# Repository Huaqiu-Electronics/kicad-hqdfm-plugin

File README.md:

# HQ DFM

<p>
    English |<a href="README_CN.md">中文<a/>
</p>

### Implementing One-Click PCB Design Flaw Analysis with HQ DFM in KiCad

The HQ DFM plugin will assist you in:

- One-click analysis of over 20 design risk issues including open circuits, disconnected traces, line spacing, and width.
- Automatically analyzing PCB design flaws and eliminating production difficulties and design defects.

After checking the design flaws, you can use the NextPCB plugin to directly add them to your shopping cart at Huaqiu.

## Features

### Design Parameter Analysis

HQ DFM will analyze the following parameters in your KiCad design:

- Layer Count
- Dimensions
- Signal Integrity
- Smallest Trace Width
- Smallest Trace Spacing
- Pad size
- Pad Spacing
- Hatched Copper Pour
- Hole Diameter
- RingHole
- Drill Hole Spacing
- Drill to Copper
- Board Edge Clearance
- Special Drill Holes
- Holes on SMD Pads
- Missing SMask Openings
- Drill Hole Density
- Surface Finish Area
- Test Point Count

## Installation

Install the latest release plugin from **Plugin and Content Manager**. Open the "Plugin and Content Manager" from the main window, Navigate to the "Plugins" section and locate "HQ DFM" in the list. Finally, Click on the "Install" button and "Apply Pending Changes" to finalize the installation process.

### About HQ DFM

[HQ DFM](https://dfm.hqpcb.com/) is an efficient PCB design software that performs one-click analysis of design risks, provides optimization solutions, and generates Gerber, BOM, and coordinate files, making design and manufacturing simpler.

you can use the HQDFM Gerber Viewer to double check your manufacturing files, adjust board parameters then add it to your NextPCB cart directly.

### About HQ PCB / NextPCB

HQ PCB specializes in reliable multilayer PCB manufacture and assembly, and like KiCad, our goal is to enable engineers to build tomorrow's electronics. NextPCB is working with KiCad to provide smart tools to simplify the progression from design to physical product. With 3 major factories catering to prototyping, mass production and PCB assembly, and over 15 years of engineering expertise, NextPCB believes our industrial experience will prove invaluable to KiCad users and the PCB design community.

We are a [KiCad Platinum Sponsor](https://www.nextpcb.com/blog/kicad-nextpcb-platinum-sponsorship).

## kicad-HQ install

### Windows

The Windows installation package can be downloaded directly using the following link:
https://www.eda.cn/data/kicad-release/kicad-huaqiu-8.0.6-x86_64.exe.zip

### Linux
The Linux version requires Flatpak installation

#### 1，Install flatpak

`sudo apt install flatpak`

#### 2，Map a domain name to a specific IP address

`sudo vim /etc/hosts`

Use vim to go to etc/host and add this line：
`175.6.14.183 kicad.huaqiu.com`

Check whether the connection is successful:
`ping kicad.huaqiu.com`

#### 3，Add a remote kicad repository

`flatpak remote-add --user repo https://kicad.huaqiu.com/kicadhuaqiu`

Check whether the addition succeeds：
`flatpak remote-ls repo`

If GPG verification is reported, go to Step 4. Otherwise, skip it

#### 4，Ignore package unsigned authentication and modify the configuration with the vim editor

`vim ~/.local/share/flatpak/repo/config`

Modify in the file:
`gpg-verify=false`

`flatpak remote-modify --no-gpg-verify repo`

Check whether the addition is successful:
`flatpak remote-ls repo`

#### 5，Install kicad

`flatpak install repo org.kicad.KiCad`

If no dependency is reported, go to the next step "6".

#### 6，Lack of SDK dependency, use domestic flathub mirror warehouse, add remote warehouse first, and then install the missing dependency:

`sudo flatpak remote-modify flathub --url=https://mirror.sjtu.edu.cn/flathub`

In case of lack org.freedesktop.Sdk/x86_64/23.08：
`flatpak install flathub org.freedesktop.Sdk/x86_64/23.08`

In case of lack org.freedesktop.Sdk//23.08：
`flatpak install flathub org.freedesktop.Sdk//23.08`

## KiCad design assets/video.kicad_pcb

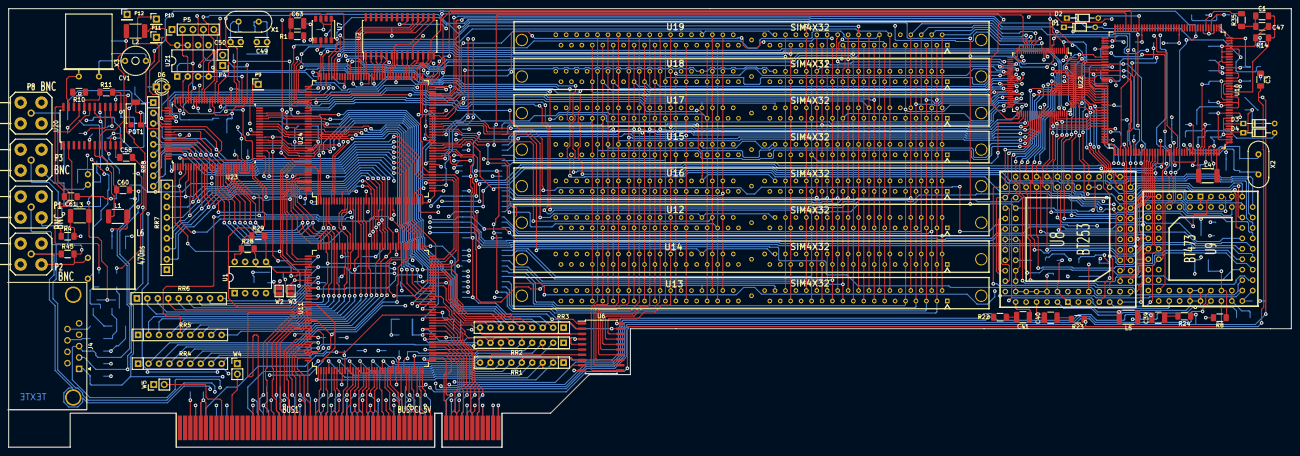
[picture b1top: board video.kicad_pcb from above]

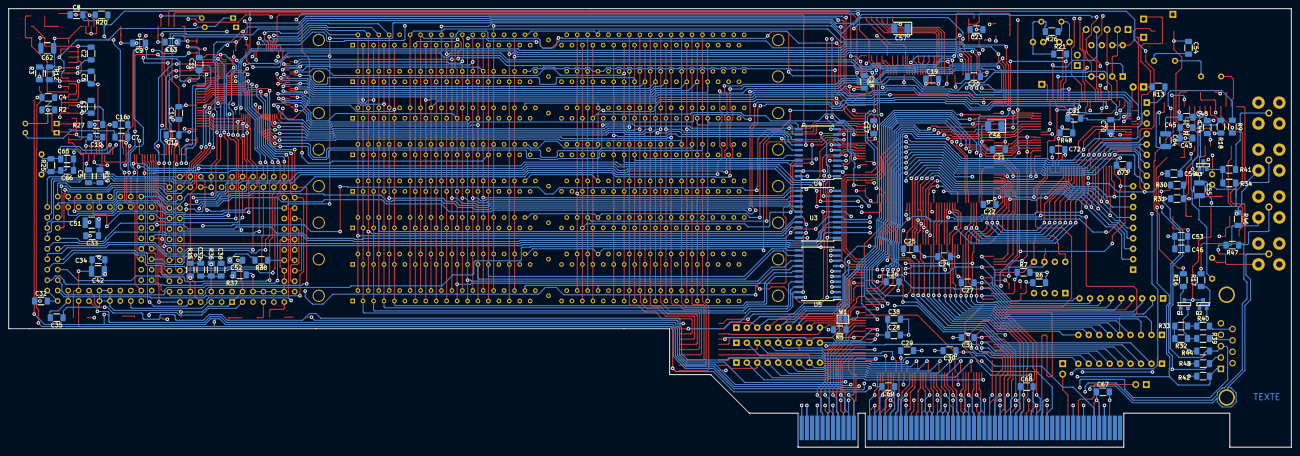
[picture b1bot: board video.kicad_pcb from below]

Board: 4 copper layers, 312.0 x 106.7 mm, 189 parts (103 on the bottom side), 371 nets.

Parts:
BUS1: BUSPCI_5V; BUSPCI
C1, C2, C3, C4, C5, C6, C7, C8, C9, C10, C11, C12, C13, C14, C15, C16, C17, C18, C19, C20, C21, C22, C23, C24, C25, C26, C27, C28, C29, C30, C31, C32, C33, C34, C35, C36, C70, C71, C72, C73: 100nF; R_1206_3216Metric_Pad1.30x1.75mm_HandSolder
C37: 100pF; R_1206_3216Metric_Pad1.30x1.75mm_HandSolder
C38, C67, C68, C69: 4,7uF; R_1206_3216Metric_Pad1.30x1.75mm_HandSolder
C39, C40, C41: 1uF; R_1210_3225Metric_Pad1.30x2.65mm_HandSolder
C42: 2.2uF; R_1210_3225Metric_Pad1.30x2.65mm_HandSolder
C43, C44, C45: 220nF; R_1206_3216Metric_Pad1.30x1.75mm_HandSolder
C46, C47: 220pF; R_1206_3216Metric_Pad1.30x1.75mm_HandSolder
C48: 22nF; R_1206_3216Metric_Pad1.30x1.75mm_HandSolder
C49, C50: 22pF; C_Disc_D3.0mm_W2.0mm_P2.50mm
C51: 22uF; R_1210_3225Metric_Pad1.30x2.65mm_HandSolder
C52: 22uF; R_1206_3216Metric_Pad1.30x1.75mm_HandSolder
C53: 330pF; R_1206_3216Metric_Pad1.30x1.75mm_HandSolder
C54: 4.7uF; R_1206_3216Metric_Pad1.30x1.75mm_HandSolder
C55: 4.7uF; R_1210_3225Metric_Pad1.30x2.65mm_HandSolder
C56, C57: 4.7uF; CP_EIA-3528-21_Kemet-B_Pad1.50x2.35mm_HandSolder
C58, C59, C60, C61: 47nF; R_1206_3216Metric_Pad1.30x1.75mm_HandSolder
C62, C63: 47uF; R_1210_3225Metric_Pad1.30x2.65mm_HandSolder
C64: 6,8uF; R_1210_3225Metric_Pad1.30x2.65mm_HandSolder
C65, C66: 22pF; R_1206_3216Metric_Pad1.30x1.75mm_HandSolder
CV1: 5/30pF; CV3-30PF
D1, D2, D3, D4: BAT46; D_DO-34_SOD68_P7.62mm_Horizontal
D6: LED; LED_D3.0mm
J4: DB9FEM; DSUB-9_Female_Horizontal_P2.77x2.84mm_EdgePinOffset14.56mm_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
L1: 2,2uH; R_1812_4532Metric_Pad1.30x3.40mm_HandSolder
L2, L3, L5: 22uH; R_1812_4532Metric_Pad1.30x3.40mm_HandSolder
L4: 22uF; R_1812_4532Metric_Pad1.30x3.40mm_HandSolder
L6: 470ns; LRTDK
P1, P2, P3, P8: BNC; subclick
P4: CONN_2; PinHeader_1x02_P2.54mm_Vertical
P5: CONN_5; PinHeader_1x05_P2.54mm_Vertical
P9, P10, P11, P12: CONN_1; PinHeader_1x01_P2.54mm_Vertical
POT1: 100K; Potentiometer_Bourns_3314G_Vertical
Q1, Q2, Q3: BC848; SOT23EBC
R1: 10; R_1206_3216Metric_Pad1.30x1.75mm_HandSolder
R2, R3: 100; R_1206_3216Metric_Pad1.30x1.75mm_HandSolder
R4, R5, R6, R7, R48: 10K; R_1206_3216Metric_Pad1.30x1.75mm_HandSolder
R8: 150; R_1206_3216Metric_Pad1.30x1.75mm_HandSolder
R9: 150K; R_1206_3216Metric_Pad1.30x1.75mm_HandSolder
R10, R11, R12, R13: 1K; R_1206_3216Metric_Pad1.30x1.75mm_HandSolder
R14, R15: 1M; R_1206_3216Metric_Pad1.30x1.75mm_HandSolder
R16, R17, R18, R19, R20, R21, R22, R23, R24: 220; R_1206_3216Metric_Pad1.30x1.75mm_HandSolder
R25, R26: 220K; R_1206_3216Metric_Pad1.30x1.75mm_HandSolder
R27: 27K; R_1206_3216Metric_Pad1.30x1.75mm_HandSolder
R28, R29: 2,2K; R_1206_3216Metric_Pad1.30x1.75mm_HandSolder
R30: 3,3K; R_1206_3216Metric_Pad1.30x1.75mm_HandSolder
R31, R32, R33, R34, R35, R36: 470; R_1206_3216Metric_Pad1.30x1.75mm_HandSolder
R37, R38: 510; R_1206_3216Metric_Pad1.30x1.75mm_HandSolder
R39, R40, R41: 68; R_1206_3216Metric_Pad1.30x1.75mm_HandSolder
R42, R43, R44, R45, R46, R47: 75; R_1206_3216Metric_Pad1.30x1.75mm_HandSolder
RR1, RR2, RR3, RR4, RR5, RR6, RR7, RR8: 8x10K; R_Array_SIP9
U1: 24C16; DIP-8_W7.62mm
U2: 4C4001; SOIC-28W_7.5x17.9mm_P1.27mm
U3, U4, U5, U6: 74LS245; SOIC-20W_7.5x12.8mm_P1.27mm
U7: AV9173; SSOP-8_3.95x5.21x3.27mm_P1.27mm
U8: BT253; PLCC84
U9: BT473; PLCC68
U10: BT812; PQFP-160_28x28mm_P0.65mm
U11: S5933_PQ160; PQFP-160_28x28mm_P0.65mm
U12, U13, U14, U15, U16, U17, U18, U19: SIM4X32; sim72
U20: TDA8501; SOIC-24W_7.5x15.4mm_P1.27mm
U21: XC1736APD8; DIP-8_W7.62mm
U22: XC4003-VQ100; TQFP-100_14x14mm_P0.5mm
U23: XC4003/PQ100; PQFP-100_14x20mm_P0.65mm
U24: XC4005-PQ160; PQFP-160_28x28mm_P0.65mm
W1: 16/32; SolderJumper-2_P1.3mm_Open_Pad1.0x1.5mm
W2: FLOAT#; SolderJumper-2_P1.3mm_Open_Pad1.0x1.5mm
W3: SERNV; SolderJumper-2_P1.3mm_Open_Pad1.0x1.5mm
W4, W5: TEST; PinHeader_1x02_P2.54mm_Vertical
X1: 10MHz; Crystal_HC18-U_Vertical
X2: 30MHz; Crystal_HC18-U_Vertical
X3: 4.433618MHz; Crystal_HC18-U_Horizontal

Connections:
+3.3V: BUS1.A21 (+3.3V), BUS1.A27 (+3.3V), BUS1.A33 (+3.3V), BUS1.A39 (+3.3V), BUS1.A45 (+3.3V), BUS1.A53 (+3.3V), BUS1.B25 (+3.3V), BUS1.B31 (+3.3V), BUS1.B36 (+3.3V), BUS1.B41 (+3.3V), BUS1.B43 (+3.3V), BUS1.B54 (+3.3V), C68.1, C69.1
+5F: C55.1, L3.2, Q1.3 (C), Q2.3 (C), Q3.3 (C)
+5V: BUS1.A5 (+5V), BUS1.A8 (+5V), BUS1.A10 (VIO), BUS1.A16 (VIO), BUS1.A59 (VIO), BUS1.A61 (+5V), BUS1.A62 (+5V), BUS1.B5 (+5V), BUS1.B6 (+5V), BUS1.B19 (VIO), BUS1.B59 (VIO), BUS1.B61 (+5V), BUS1.B62 (+5V), C9.1, C10.1, C11.1, C15.1, C17.1, C18.1, C19.1, C20.1, C21.1, C22.1, C24.1, C25.1, C26.1, C27.1, C28.1, C29.1, C30.1, C31.1, C38.1, C56.1, C57.1, C67.1, C70.1, C71.1, C72.1, C73.1, D2.2 (K), D4.2 (K), L2.1, L3.1, L4.1, L5.1, R1.2, R4.2, R5.2, R6.2, R7.2, R13.1, R28.1, R29.1, R48.1, RR1.1 (COM), RR2.1 (COM), RR3.1 (COM), RR4.1 (COM), RR5.1 (COM), RR6.1 (COM), RR7.1 (COM), RR8.1 (COM), U1.7 (WP), U1.8 (VCC), U2.10 (VCC), U3.20 (VCC), U4.20 (VCC), U5.20 (VCC), U6.20 (VCC), U10.31 (VCC), U10.45 (VCC), U10.57 (VCC), U10.76 (VCC), U10.91 (VCC), U10.102 (VCC), U10.112 (VCC), U11.11 (VCC), U11.31 (VCC), U11.51 (VCC), U11.71 (VCC), U11.91 (VCC), U11.111 (VCC), U11.131 (VCC), U11.151 (VCC), U12.10 (VCC), U12.30 (VCC), U12.59 (VCC), U13.10 (VCC), U13.30 (VCC), U13.59 (VCC), U14.10 (VCC), U14.30 (VCC), U14.59 (VCC), U15.10 (VCC), U15.30 (VCC), U15.59 (VCC), U16.10 (VCC), U16.30 (VCC), U16.59 (VCC), U17.10 (VCC), U17.30 (VCC), U17.59 (VCC), U18.10 (VCC), U18.30 (VCC), U18.59 (VCC), U19.10 (VCC), U19.30 (VCC), U19.59 (VCC), U21.7 (VPP), U21.8 (VCC), U22.12 (VCC), U22.22 (M1/RD), U22.24 (M0/RT), U22.25 (VCC), U22.26 (M2), U22.37 (VCC), U22.51 (VCC), U22.63 (VCC), U22.75 (VCC), U22.89 (VCC), U22.100 (VCC), U23.3 (VCC), U23.15 (VCC), U23.28 (VCC), U23.40 (VCC), U23.54 (VCC), U23.66 (VCC), U23.78 (VCC), U23.92 (VCC), U24.20 (VCC), U24.38 (M1), U24.40 (M0), U24.41 (VCC), U24.42 (M2), U24.60 (VCC), U24.81 (VCC), U24.100 (VCC), U24.120 (VCC), U24.142 (VCC), U24.160 (VCC)
/ACCES_RAM-: U3.19 (CE), U4.19 (CE), U5.19 (CE), U6.19 (CE), U22.21 (SGCK2), U24.56
/ACQ_ON: U22.13, U24.48 (LDC)
/ADR2: U11.68 (ADR2), U23.48, U24.137
/ADR3: U11.67 (ADR3), U23.44, U24.138
/ADR4: U11.66 (ADR4), U23.43, U24.139
/ADR5: U11.64 (ADR5), U23.42, U24.140
/ADR6: U11.132 (ADR6), U23.39 (P39/INIT), U24.143
/BE-0: U11.87 (BE0#), U23.38, U24.144
/BE-1: U11.63 (BE1#), U23.37, U24.145
/BE-2: U11.62 (BE2#), U23.36, U24.146
/BE-3: U11.60 (BE3#), U23.35, U24.147
/BLANK-: U9.7 (BLANK), U22.8, U24.53
/BLUE_IN: P3.1 (In), R22.1, R46.1
/BLUE_OUT: C60.2, J4.3, R44.2, U9.39 (BLU)
/BPCLK: U11.140 (BPCLK), U23.30 (PGCK2)
/BT812_RD-: U10.86 (RD), U23.71
/BT812_WR-: U10.83 (WR), U23.70
/CAS0-: U12.40 (CAS0), U13.40 (CAS0), U14.40 (CAS0), U15.40 (CAS0), U16.40 (CAS0), U17.40 (CAS0), U18.40 (CAS0), U19.40 (CAS0), U24.57
/CAS1-: U12.41 (CAS1), U13.41 (CAS1), U14.41 (CAS1), U15.41 (CAS1), U16.41 (CAS1), U17.41 (CAS1), U18.41 (CAS1), U19.41 (CAS1), U24.58
/CAS2-: U12.42 (CAS2), U13.42 (CAS2), U14.42 (CAS2), U15.42 (CAS2), U16.42 (CAS2), U17.42 (CAS2), U18.42 (CAS2), U19.42 (CAS2), U24.59 (P59-INIT)
/CAS3-: U12.43 (CAS3), U13.43 (CAS3), U14.43 (CAS3), U15.43 (CAS3), U16.43 (CAS3), U17.43 (CAS3), U18.43 (CAS3), U19.43 (CAS3), U24.62
/CLAMP: U8.37 (ZERO), U8.59 (CLAMP), U22.7, U24.75
/CLKCAD: U8.38 (BCLOCK), U8.39 (GCLOCK), U8.40 (RCLOCK), U22.2 (PGCK1), U24.77
/CLKCDA: U9.9 (CLOCK), U22.79 (PGCK4), U24.76
/CSYNC-OUT: R30.2, U9.8 (SYNC), U22.9 (P/A15), U24.13 (TMS)
/CSYNCIN-: U8.8 (CSYNC), U24.54
/C_OUT: J4.8, R39.1
/DQ0: RR7.2, U3.2 (A0), U8.16 (D0), U9.14 (D0), U10.92 (D0), U11.100 (DQ0), U23.13, U24.21
/DQ1: RR7.3, U3.3 (A1), U8.15 (D1), U9.15 (D1), U10.93 (D1), U11.99 (DQ1), U23.12, U24.22
/DQ2: RR7.4, U3.4 (A2), U8.14 (D2), U9.16 (D2), U10.94 (D2), U11.98 (DQ2), U23.11, U24.23
/DQ3: RR7.5, U3.5 (A3), U8.13 (D3), U9.17 (D3), U10.95 (D3), U11.96 (DQ3), U23.7 (P7/TDI), U24.24
/DQ4: RR7.6, U3.6 (A4), U8.12 (D4), U9.18 (D4), U10.96 (D4), U11.95 (DQ4), U23.9 (P9/TMS), U24.25
/DQ5: RR7.7, U3.7 (A5), U8.11 (D5), U9.19 (D5), U10.97 (D5), U11.94 (DQ5), U23.8 (P8/TCK), U24.26
/DQ6: RR7.8, U3.8 (A6), U8.10 (D6), U9.20 (D6), U10.99 (D6), U11.92 (DQ6), U23.6, U24.27
/DQ7: RR7.9, U3.9 (A7), U8.9 (D7), U9.21 (D7), U10.100 (D7), U11.88 (DQ7), U23.5 (PGCK1), U24.28
/DQ8: RR8.9, U4.2 (A0), U11.86 (DQ8), U23.97, U24.32
/DQ9: RR8.8, U4.3 (A1), U11.84 (DQ9), U23.96, U24.33
/DQ10: RR8.7, U4.4 (A2), U11.83 (DQ10), U23.95, U24.34
/DQ11: RR8.6, U4.5 (A3), U11.82 (DQ11), U23.94, U24.35
/DQ12: RR8.5, U4.6 (A4), U11.80 (DQ12), U23.93, U24.36
/DQ13: RR8.4, U4.7 (A5), U11.79 (DQ13), U23.90, U24.45
/DQ14: RR8.3, U4.8 (A6), U11.78 (DQ14), U23.88, U24.46
/DQ15: RR8.2, U4.9 (A7), U11.76 (DQ15), U23.89, U24.47
/DQ16: RR4.7, U5.2 (A0), U11.157 (DQ16)
/DQ17: RR4.9, U5.3 (A1), U11.145 (DQ17)
/DQ18: RR6.6, U5.4 (A2), U11.133 (DQ18)
/DQ19: RR6.8, U5.5 (A3), U11.125 (DQ19)
/DQ20: RR6.3, U5.6 (A4), U11.117 (DQ20)
/DQ21: RR5.6, U5.7 (A5), U11.105 (DQ21)
/DQ22: RR4.3, U5.8 (A6), U11.93 (DQ22)
/DQ23: RR4.5, U5.9 (A7), U11.85 (DQ23)
/DQ24: RR3.3, U6.2 (A0), U11.77 (DQ24)
/DQ25: RR3.9, U6.3 (A1), U11.65 (DQ25)
/DQ26: RR2.8, U6.4 (A2), U11.53 (DQ26)
/DQ27: RR2.5, U6.5 (A3), U11.45 (DQ27)
/DQ28: RR2.3, U6.6 (A4), U11.37 (DQ28)
/DQ29: RR1.8, U6.7 (A5), U11.25 (DQ29)
/DQ30: RR1.5, U6.8 (A6), U11.13 (DQ30)
/DQ31: RR1.3, U6.9 (A7), U11.5 (DQ31)
/ESVIDEO-RVB/OE_RVB-: U8.57 (OE), U9.29 (CR2)
/ESVIDEO-RVB/REF+: R37.2, U8.64 (BREF+), U8.65 (GREF+), U8.66 (RREF+), U8.71 (IOUT5), U8.73 (IOUT4), U8.76 (IOUT3), U8.78 (IOUT2), U8.80 (IOUT1), U8.82 (IOUT0)
/ESVIDEO-RVB/VAA: C33.1, C34.1, C35.1, C42.1, C51.1, C52.1, L5.2, U8.1 (VAA), U8.43 (VAA), U8.44 (VAA), U8.84 (VAA), U9.1 (VAA), U9.2 (VAA), U9.33 (VAA), U9.34 (VAA), U9.35 (VAA), U9.36 (VAA)
/F_PALIN: U10.104 (CLKX1), U24.43 (PGCK2)
/GREEN_IN: C3.2, P2.1 (In), R23.1, R45.1
/GREEN_OUT: C59.2, J4.2, R43.2, U9.38 (GRE)
/HD_PAL-: U10.36 (HRESET), U24.52
/IRQ-: U11.124 (IRQ#), U24.149
/IRQ_SRL: RR2.7, U11.57 (EA0), U24.134
/MXA0: U12.12 (A0), U13.12 (A0), U14.12 (A0), U15.12 (A0), U16.12 (A0), U17.12 (A0), U18.12 (A0), U19.12 (A0), U24.128
/MXA1: U12.13 (A1), U13.13 (A1), U14.13 (A1), U15.13 (A1), U16.13 (A1), U17.13 (A1), U18.13 (A1), U19.13 (A1), U24.127
/MXA2: U12.14 (A2), U13.14 (A2), U14.14 (A2), U15.14 (A2), U16.14 (A2), U17.14 (A2), U18.14 (A2), U19.14 (A2), U24.126
/MXA3: U12.15 (A3), U13.15 (A3), U14.15 (A3), U15.15 (A3), U16.15 (A3), U17.15 (A3), U18.15 (A3), U19.15 (A3), U24.125
/MXA4: U12.16 (A4), U13.16 (A4), U14.16 (A4), U15.16 (A4), U16.16 (A4), U17.16 (A4), U18.16 (A4), U19.16 (A4), U24.124
/MXA5: U12.17 (A5), U13.17 (A5), U14.17 (A5), U15.17 (A5), U16.17 (A5), U17.17 (A5), U18.17 (A5), U19.17 (A5), U24.123
/MXA6: U12.18 (A6), U13.18 (A6), U14.18 (A6), U15.18 (A6), U16.18 (A6), U17.18 (A6), U18.18 (A6), U19.18 (A6), U24.116
/MXA7: U12.28 (A7), U13.28 (A7), U14.28 (A7), U15.28 (A7), U16.28 (A7), U17.28 (A7), U18.28 (A7), U19.28 (A7), U24.115
/MXA8: U12.31 (A8), U13.31 (A8), U14.31 (A8), U15.31 (A8), U16.31 (A8), U17.31 (A8), U18.31 (A8), U19.31 (A8), U24.114 (P114-RDY)
/MXA9: U12.32 (A9), U13.32 (A9), U14.32 (A9), U15.32 (A9), U16.32 (A9), U17.32 (A9), U18.32 (A9), U19.32 (A9), U24.113
/MXA10: U12.19 (A10), U13.19 (A10), U14.19 (A10), U15.19 (A10), U16.19 (A10), U17.19 (A10), U18.19 (A10), U19.19 (A10), U24.109
/OE_PAL-: U9.28 (CR1), U10.46 (VTU_EN), U10.47 (PIXEL_EN)
/PCA0: U8.17 (A0), U9.24 (RS0), U10.84 (RS0), U23.65
/PCA1: U8.18 (A1), U9.25 (RS1), U10.85 (RS1), U23.64
/PCA2: U8.19 (A2), U9.26 (RS2), U23.63
/PTADR-: RR5.5, U11.107 (PTADR#), U23.24 (SGCK2), U24.14
/PTATN-: RR5.2, U11.114 (PTATN#), U23.18, U24.4
/PTBE-0: U11.116 (PTBE0#), U23.20, U24.158
/PTBE-1: U11.118 (PTBE1#), U23.21, U24.157
/PTBE-2: U11.119 (PTBE2#), U23.22, U24.156
/PTBE-3: U11.120 (PTBE3#), U23.23, U24.155
/PTBURST: U11.112 (PTBURST#), U23.17, U24.5
/PTNUM0: U11.123 (PTNUM0), U23.34, U24.150
/PTNUM1: U11.122 (PTNUM1), U23.32, U24.154
/PTRDY-: RR6.2, U11.115 (PTRDY#), U23.19, U24.3
/PTWR: U11.108 (PTWR), U23.16, U24.12
/RAS0-: U19.34 (RAS2), U19.44 (RAS0), U24.74
/RAS1-: U18.34 (RAS2), U18.44 (RAS0), U24.73
/RAS2-: U17.34 (RAS2), U17.44 (RAS0), U24.69
/RAS3-: U15.34 (RAS2), U15.44 (RAS0), U24.68
/RAS4-: U16.34 (RAS2), U16.44 (RAS0), U24.67
/RAS5-: U12.34 (RAS2), U12.44 (RAS0), U24.66
/RAS6-: U14.34 (RAS2), U14.44 (RAS0), U24.65
/RAS7-: U13.34 (RAS2), U13.44 (RAS0), U24.64
/RDCAD-: U8.20 (RD), U23.74 (P74/BUSY)
/RDCDA-: U9.22 (WR), U23.72
/RDEMPTY: U11.106 (RDEMPTY), U24.15
/RDFIFO-: RR5.7, U11.104 (RDFIFO#), U24.16
/RED_IN: C4.2, P1.1 (In), R24.1, R47.1
/RED_OUT: C58.2, J4.1, R42.2, U9.37 (RED)
/SELECT-: RR3.4, U11.75 (SELECT#), U23.45, U24.135
/SYSRST-: U10.87 (RESET), U11.126 (SYSRST#), U23.1, U24.148
/TVB0: U8.32 (B0), U9.61 (B0), U10.55 (B0), U22.92
/TVB1: U8.31 (B1), U9.62 (B1), U10.54 (B1), U22.93
/TVB2: U8.30 (B2), U9.63 (B2), U10.53 (B2), U22.94
/TVB3: U8.29 (B3), U9.64 (B3), U10.52 (B3), U22.95 (P91)
/TVB4: U8.28 (B4), U9.65 (B4), U10.51 (B4), U22.96
/TVB5: U8.27 (B5), U9.66 (B5), U10.50 (B5), U22.97
/TVB6: U8.26 (B6), U9.67 (B6), U10.49 (B6), U22.98
/TVB7: U8.25 (B7), U9.68 (B7), U10.48 (B7), U22.99 (SGCK1)
/TVG0: U8.48 (G0), U9.53 (G0), U10.74 (G0), U22.67
/TVG1: U8.47 (G1), U9.54 (G1), U10.73 (G1), U22.68
/TVG2: U8.46 (G2), U9.55 (G2), U10.72 (G2), U22.69
/TVG3: U8.45 (G3), U9.56 (G3), U10.71 (G3), U22.70
/TVG4: U8.36 (G4), U9.57 (G4), U10.70 (G4), U22.71 (P71/RDY)
/TVG5: U8.35 (G5), U9.58 (G5), U10.69 (G5), U22.78
/TVG6: U8.34 (G6), U9.59 (G6), U10.68 (G6), U22.80
/TVG7: U8.33 (G7), U9.60 (G7), U10.67 (G7), U22.81
/TVI0: U9.10 (OL0), U24.108
/TVI1: U9.11 (OL1), U24.107
/TVR0: U8.56 (R0), U9.45 (R0), U10.65 (R0), U22.82
/TVR1: U8.55 (R1), U9.46 (R1), U10.64 (R1), U22.83
/TVR2: U8.54 (R2), U9.47 (R2), U10.63 (R2), U22.84
/TVR3: U8.53 (R3), U9.48 (R3), U10.62 (R3), U22.85
/TVR4: U8.52 (R4), U9.49 (R4), U10.61 (R4), U22.86
/TVR5: U8.51 (R5), U9.50 (R5), U10.60 (R5), U22.87
/TVR6: U8.50 (R6), U9.51 (R6), U10.59 (R6), U22.90
/TVR7: U8.49 (R7), U9.52 (R7), U10.58 (R7), U22.91
/TVRAM0: U3.18 (B0), U12.2 (DQ0), U13.2 (DQ0), U14.2 (DQ0), U15.2 (DQ0), U16.2 (DQ0), U17.2 (DQ0), U18.2 (DQ0), U19.2 (DQ0), U22.17
/TVRAM1: U3.17 (B1), U12.4 (DQ1), U13.4 (DQ1), U14.4 (DQ1), U15.4 (DQ1), U16.4 (DQ1), U17.4 (DQ1), U18.4 (DQ1), U19.4 (DQ1), U22.19
/TVRAM2: U3.16 (B2), U12.6 (DQ2), U13.6 (DQ2), U14.6 (DQ2), U15.6 (DQ2), U16.6 (DQ2), U17.6 (DQ2), U18.6 (DQ2), U19.6 (DQ2), U22.20
/TVRAM3: U3.15 (B3), U12.8 (DQ3), U13.8 (DQ3), U14.8 (DQ3), U15.8 (DQ3), U16.8 (DQ3), U17.8 (DQ3), U18.8 (DQ3), U19.8 (DQ3), U22.18
/TVRAM4: U3.14 (B4), U12.20 (DQ4), U13.20 (DQ4), U14.20 (DQ4), U15.20 (DQ4), U16.20 (DQ4), U17.20 (DQ4), U18.20 (DQ4), U19.20 (DQ4), U22.28 (P/HDC)
/TVRAM5: U3.13 (B5), U12.22 (DQ5), U13.22 (DQ5), U14.22 (DQ5), U15.22 (DQ5), U16.22 (DQ5), U17.22 (DQ5), U18.22 (DQ5), U19.22 (DQ5), U22.29
/TVRAM6: U3.12 (B6), U12.24 (DQ6), U13.24 (DQ6), U14.24 (DQ6), U15.24 (DQ6), U16.24 (DQ6), U17.24 (DQ6), U18.24 (DQ6), U19.24 (DQ6), U22.31
/TVRAM7: U3.11 (B7), U12.26 (DQ7), U13.26 (DQ7), U14.26 (DQ7), U15.26 (DQ7), U16.26 (DQ7), U17.26 (DQ7), U18.26 (DQ7), U19.26 (DQ7), U22.32
/TVRAM8: U4.18 (B0), U12.49 (DQ8), U13.49 (DQ8), U14.49 (DQ8), U15.49 (DQ8), U16.49 (DQ8), U17.49 (DQ8), U18.49 (DQ8), U19.49 (DQ8), U22.33
/TVRAM9: U4.17 (B1), U12.51 (DQ9), U13.51 (DQ9), U14.51 (DQ9), U15.51 (DQ9), U16.51 (DQ9), U17.51 (DQ9), U18.51 (DQ9), U19.51 (DQ9), U22.34
/TVRAM10: U4.16 (B2), U12.53 (DQ10), U13.53 (DQ10), U14.53 (DQ10), U15.53 (DQ10), U16.53 (DQ10), U17.53 (DQ10), U18.53 (DQ10), U19.53 (DQ10), U22.35
/TVRAM11: U4.15 (B3), U12.55 (DQ11), U13.55 (DQ11), U14.55 (DQ11), U15.55 (DQ11), U16.55 (DQ11), U17.55 (DQ11), U18.55 (DQ11), U19.55 (DQ11), U22.36 (P36/INIT)
/TVRAM12: U4.14 (B4), U12.57 (DQ12), U13.57 (DQ12), U14.57 (DQ12), U15.57 (DQ12), U16.57 (DQ12), U17.57 (DQ12), U18.57 (DQ12), U19.57 (DQ12), U22.39
/TVRAM13: U4.13 (B5), U12.61 (DQ13), U13.61 (DQ13), U14.61 (DQ13), U15.61 (DQ13), U16.61 (DQ13), U17.61 (DQ13), U18.61 (DQ13), U19.61 (DQ13), U22.40
/TVRAM14: U4.12 (B6), U12.63 (DQ14), U13.63 (DQ14), U14.63 (DQ14), U15.63 (DQ14), U16.63 (DQ14), U17.63 (DQ14), U18.63 (DQ14), U19.63 (DQ14), U22.41
/TVRAM15: U4.11 (B7), U12.65 (DQ15), U13.65 (DQ15), U14.65 (DQ15), U15.65 (DQ15), U16.65 (DQ15), U17.65 (DQ15), U18.65 (DQ15), U19.65 (DQ15), U22.42
/TVRAM16: U5.18 (B0), U12.3 (DQ16), U13.3 (DQ16), U14.3 (DQ16), U15.3 (DQ16), U16.3 (DQ16), U17.3 (DQ16), U18.3 (DQ16), U19.3 (DQ16), U22.43
/TVRAM17: U5.17 (B1), U12.5 (DQ17), U13.5 (DQ17), U14.5 (DQ17), U15.5 (DQ17), U16.5 (DQ17), U17.5 (DQ17), U18.5 (DQ17), U19.5 (DQ17), U22.44
/TVRAM18: U5.16 (B2), U12.7 (DQ18), U13.7 (DQ18), U14.7 (DQ18), U15.7 (DQ18), U16.7 (DQ18), U17.7 (DQ18), U18.7 (DQ18), U19.7 (DQ18), U22.45
/TVRAM19: U5.15 (B3), U12.9 (DQ19), U13.9 (DQ19), U14.9 (DQ19), U15.9 (DQ19), U16.9 (DQ19), U17.9 (DQ19), U18.9 (DQ19), U19.9 (DQ19), U22.46
/TVRAM20: U5.14 (B4), U12.21 (DQ20), U13.21 (DQ20), U14.21 (DQ20), U15.21 (DQ20), U16.21 (DQ20), U17.21 (DQ20), U18.21 (DQ20), U19.21 (DQ20), U22.47
/TVRAM21: U5.13 (B5), U12.23 (DQ21), U13.23 (DQ21), U14.23 (DQ21), U15.23 (DQ21), U16.23 (DQ21), U17.23 (DQ21), U18.23 (DQ21), U19.23 (DQ21), U22.48 (SGCK3)
/TVRAM22: U5.12 (B6), U12.25 (DQ22), U13.25 (DQ22), U14.25 (DQ22), U15.25 (DQ22), U16.25 (DQ22), U17.25 (DQ22), U18.25 (DQ22), U19.25 (DQ22), U22.53
/TVRAM23: U5.11 (B7), U12.27 (DQ23), U13.27 (DQ23), U14.27 (DQ23), U15.27 (DQ23), U16.27 (DQ23), U17.27 (DQ23), U18.27 (DQ23), U19.27 (DQ23), U22.54 (PGCK3)
/TVRAM24: U6.18 (B0), U12.50 (DQ24), U13.50 (DQ24), U14.50 (DQ24), U15.50 (DQ24), U16.50 (DQ24), U17.50 (DQ24), U18.50 (DQ24), U19.50 (DQ24), U22.55
/TVRAM25: U6.17 (B1), U12.52 (DQ25), U13.52 (DQ25), U14.52 (DQ25), U15.52 (DQ25), U16.52 (DQ25), U17.52 (DQ25), U18.52 (DQ25), U19.52 (DQ25), U22.56
/TVRAM26: U6.16 (B2), U12.54 (DQ26), U13.54 (DQ26), U14.54 (DQ26), U15.54 (DQ26), U16.54 (DQ26), U17.54 (DQ26), U18.54 (DQ26), U19.54 (DQ26), U22.57
/TVRAM27: U6.15 (B3), U12.56 (DQ27), U13.56 (DQ27), U14.56 (DQ27), U15.56 (DQ27), U16.56 (DQ27), U17.56 (DQ27), U18.56 (DQ27), U19.56 (DQ27), U22.58
/TVRAM28: U6.14 (B4), U12.58 (DQ28), U13.58 (DQ28), U14.58 (DQ28), U15.58 (DQ28), U16.58 (DQ28), U17.58 (DQ28), U18.58 (DQ28), U19.58 (DQ28), U22.59
/TVRAM29: U6.13 (B5), U12.60 (DQ29), U13.60 (DQ29), U14.60 (DQ29), U15.60 (DQ29), U16.60 (DQ29), U17.60 (DQ29), U18.60 (DQ29), U19.60 (DQ29), U22.60
/TVRAM30: U6.12 (B6), U12.62 (DQ30), U13.62 (DQ30), U14.62 (DQ30), U15.62 (DQ30), U16.62 (DQ30), U17.62 (DQ30), U18.62 (DQ30), U19.62 (DQ30), U22.61
/TVRAM31: U6.11 (B7), U12.64 (DQ31), U13.64 (DQ31), U14.64 (DQ31), U15.64 (DQ31), U16.64 (DQ31), U17.64 (DQ31), U18.64 (DQ31), U19.64 (DQ31), U22.62
/VD_PAL-: U10.34 (VRESET), U24.37 (SGCK2)
/WRAM-: U12.47 (R/W), U13.47 (R/W), U14.47 (R/W), U15.47 (R/W), U16.47 (R/W), U17.47 (R/W), U18.47 (R/W), U19.47 (R/W), U24.63
/WRCAD-: U8.24 (WR), U23.69
/WRCDA-: U9.23 (RD), U23.73
/WRFIFDO-: RR5.8, U11.102 (WRFIFO#), U24.18
/WRFULL: U11.103 (WRFULL), U24.17
/WRITE_RAM: U3.1 (A->B), U4.1 (A->B), U5.1 (A->B), U6.1 (A->B), U24.55
/X_CLK: U22.74 (CCLK), U23.86, U24.119 (CCLK)
/X_DATA: U22.72 (DIN), U24.118 (DOUT-SGI4)
/X_DONE: U22.50 (DONE), U23.83, U24.80 (DONE)
/X_IRQ: RR5.4, U11.109 (EA8), U24.11
/X_PROG-: U22.52 (PROG), U23.84, U24.82 (PROG)
/Y_OUT: J4.9, R40.2
/buspci.sch/EA1: RR2.6, U11.61 (EA1)
/buspci.sch/EA2: RR3.8, U11.69 (EA2)
/buspci.sch/EA3: RR3.6, U11.73 (EA3)
/buspci.sch/EA4: RR3.2, U11.81 (EA4)
/buspci.sch/EA5: RR4.4, U11.89 (EA5)
/buspci.sch/EA6: RR4.2, U11.97 (EA6)
/buspci.sch/EA7: RR5.9, U11.101 (EA7)
/buspci.sch/EA9: RR5.3, U11.113 (EA9)
/buspci.sch/EA10: RR6.9, U11.121 (EA10)
/buspci.sch/EA11: RR6.7, U11.129 (EA11)
/buspci.sch/EA12: RR6.5, U11.137 (EA12)
/buspci.sch/EA13: RR6.4, U11.141 (EA13)
/buspci.sch/EA14: RR4.8, U11.149 (EA14/FWE)
/buspci.sch/EA15: RR4.6, U11.153 (EA15/FRF)
/buspci.sch/EQ0: RR1.2, U11.1 (EQ0)
/buspci.sch/EQ1: RR1.4, U11.9 (EQ1)
/buspci.sch/EQ2: RR1.6, U11.17 (EQ2)
/buspci.sch/EQ3: RR1.7, U11.21 (EQ3)
/buspci.sch/EQ4: RR1.9, U11.29 (EQ4/FWC#)
/buspci.sch/EQ5: RR2.4, U11.33 (EQ5/FRC#)
/buspci.sch/EQ6: RR2.2, U11.41 (EQ6/AMREN)
/buspci.sch/EQ7: RR2.9, U11.49 (EQ7/AMWEN)
/buspci.sch/P_AD0: BUS1.A58 (AD[00]), U11.56 (AD0)
/buspci.sch/P_AD1: BUS1.B58 (AD[01]), U11.55 (AD1)
/buspci.sch/P_AD2: BUS1.A57 (AD[02]), U11.54 (AD2)
/buspci.sch/P_AD3: BUS1.B56 (AD[03]), U11.52 (AD3)
/buspci.sch/P_AD4: BUS1.A55 (AD[04]), U11.48 (AD4)
/buspci.sch/P_AD5: BUS1.B55 (AD[05]), U11.47 (AD5)
/buspci.sch/P_AD6: BUS1.A54 (AD[06]), U11.46 (AD6)
/buspci.sch/P_AD7: BUS1.B53 (AD[07]), U11.44 (AD7)
/buspci.sch/P_AD8: BUS1.B52 (AD[08]), U11.42 (AD8)
/buspci.sch/P_AD9: BUS1.A49 (AD[09]), U11.40 (AD9)
/buspci.sch/P_AD10: BUS1.B48 (AD[10]), U11.39 (AD10)
/buspci.sch/P_AD11: BUS1.A47 (AD[11]), U11.38 (AD11)
/buspci.sch/P_AD12: BUS1.B47 (AD[12]), U11.36 (AD12)
/buspci.sch/P_AD13: BUS1.A46 (AD[13]), U11.35 (AD13)
/buspci.sch/P_AD14: BUS1.B45 (AD[14]), U11.34 (AD14)
/buspci.sch/P_AD15: BUS1.A44 (AD[15]), U11.32 (AD15)
/buspci.sch/P_AD16: BUS1.A32 (AD[16]), U11.14 (AD16)
/buspci.sch/P_AD17: BUS1.B32 (AD[17]), U11.12 (AD17)
/buspci.sch/P_AD18: BUS1.A31 (AD[18]), U11.8 (AD18)
/buspci.sch/P_AD19: BUS1.B30 (AD[19]), U11.7 (AD19)
/buspci.sch/P_AD20: BUS1.A29 (AD[20]), U11.6 (AD20)
/buspci.sch/P_AD21: BUS1.B29 (AD[21]), U11.4 (AD21)
/buspci.sch/P_AD22: BUS1.A28 (AD[22]), U11.3 (AD22)
/buspci.sch/P_AD23: BUS1.B27 (AD[23]), U11.2 (AD23)
/buspci.sch/P_AD24: BUS1.A25 (AD[24]), U11.158 (AD24)
/buspci.sch/P_AD25: BUS1.B24 (AD[25]), U11.156 (AD25)
/buspci.sch/P_AD26: BUS1.A23 (AD[26]), U11.155 (AD26)
/buspci.sch/P_AD27: BUS1.B23 (AD[27]), U11.154 (AD27)
/buspci.sch/P_AD28: BUS1.A22 (AD[28]), U11.152 (AD28)
/buspci.sch/P_AD29: BUS1.B21 (AD[29]), U11.148 (AD29)
/buspci.sch/P_AD30: BUS1.A20 (AD[30]), U11.147 (AD30)
/buspci.sch/P_AD31: BUS1.B20 (AD[31]), U11.146 (AD31)
/buspci.sch/P_CLK: BUS1.B16 (CLK), U11.142 (CLK)
/buspci.sch/P_C/BE0#: BUS1.A52 (C/BE#[0]), U11.43 (C/BE0#)
/buspci.sch/P_C/BE1#: BUS1.B44 (C/BE#[1]), U11.28 (C/BE1#)
/buspci.sch/P_C/BE2#: BUS1.B33 (C/BE#[2]), U11.15 (C/BE2#)
/buspci.sch/P_C/BE3#: BUS1.B26 (C/BE#[3]), U11.159 (C/BE3#)
/buspci.sch/P_DEVSEL#: BUS1.B37 (DEVSEL#), U11.20 (DEVSEL#)
/buspci.sch/P_FRAME#: BUS1.A34 (FRAME#), U11.16 (FRAME#)
/buspci.sch/P_GNT#: BUS1.A17 (GNT#), U11.143 (GNT#)
/buspci.sch/P_IDSEL: BUS1.A26 (IDSEL), U11.160 (IDSEL)
/buspci.sch/P_INTA#: BUS1.A6 (INTA#), U11.58 (INTA#)
/buspci.sch/P_IRDY#: BUS1.B35 (IRDY#), U11.18 (IRDY#)
/buspci.sch/P_LOCK#: BUS1.B39 (LOCK#), U11.23 (LOCK#)
/buspci.sch/P_PAR: BUS1.A43 (PAR), U11.27 (PAR)
/buspci.sch/P_PERR#: BUS1.B40 (PERR#), U11.24 (PERR#)
/buspci.sch/P_REQ#: BUS1.B18 (REQ#), U11.144 (REQ#)
/buspci.sch/P_RST#: BUS1.A15 (RST#), U11.139 (RST#)
/buspci.sch/P_SERR#: BUS1.B42 (SERR#), U11.26 (SERR#)
/buspci.sch/P_STOP#: BUS1.A38 (STOP#), U11.22 (STOP#)
/buspci.sch/P_TRDY#: BUS1.A36 (TRDY#), U11.19 (TRDY#)
/graphic/14MHZOUT: U7.6 (CKKOUT), U24.95
/graphic/CCLK: P5.2, U21.2 (CLK), U23.77 (CCLK)
/graphic/CLK10MHz: R21.2, U23.57 (PGCK3), U24.2 (PGCK1)
/graphic/CSIO-: U23.61, U24.159 (SGCK1)
/graphic/DIN: P5.3, U21.1 (DATA), U23.75 (DIN/D0)
/graphic/DONE: P5.4, U23.53 (DONE)
/graphic/HDOUT: U7.1 (FSIGIN), U24.7 (TCK)
/graphic/HDREFOUT: U7.2 (FREFIN), U24.6 (TDI)
/graphic/IA0: U2.6 (A0), U24.94 (P93)
/graphic/IA1: U2.7 (A1), U24.92
/graphic/IA2: U2.8 (A2), U24.88
/graphic/IA3: U2.9 (A3), U24.87
/graphic/IA4: U2.11 (A4), U24.86
/graphic/IA5: U2.12 (A5), U24.85
/graphic/IA6: U2.13 (A6), U24.83
/graphic/IA7: U2.14 (A7), U24.78 (SGCK3)
/graphic/IA8: U2.15 (A8), U24.93
/graphic/IA9: U2.5 (A9), U24.96
/graphic/ICAS-: U2.17 (CAS), U24.104
/graphic/ID0: U2.1 (D0), U24.102
/graphic/ID1: U2.2 (D1), U24.99 (P90)
/graphic/ID2: U2.18 (D2), U24.105
/graphic/ID3: U2.19 (D3), U24.106
/graphic/IOE-: U2.16 (OE), U24.103
/graphic/IRAS-: U2.4 (RAS), U24.97
/graphic/IWR-: U2.3 (WR), U24.98
/graphic/LED: D6.2 (K), U23.81
/graphic/PROG*: P5.5, U21.3 (RAZ/OE), U21.4 (CE), U23.55 (PROG)
/graphic/RESERV1: U23.59, U24.44 (HDC)
/graphic/VOSC: C23.1, C63.1, R1.1, U7.4 (FS0), U7.5 (OE), U7.7 (VCC)
/graphic/XTAL_I: C50.1, R26.1, U23.56, X1.2
/graphic/X_DIN: U23.85, U24.117 (DIN)
/modul/CHROM: R16.2, U20.14 (C/OUT)
/modul/CVBS: R18.2, U20.16 (CVBS)
/modul/CVBSOUT: P8.1 (In), R41.1
/modul/LUM: R17.2, U20.19 (Y/OUT)
/pal-ntsc.sch/C-VIDEO: D3.2 (K), D4.1 (A), R2.1, U10.125 (VID0_C)
/pal-ntsc.sch/VAF: C2.1, C12.1, C13.1, C14.1, C62.1, L4.2, R12.2, U10.1 (VAA), U10.2 (VAA), U10.39 (VAA), U10.40 (VAA), U10.41 (VAA), U10.42 (VAA), U10.43 (VAA), U10.78 (VAA), U10.79 (VAA), U10.80 (VAA), U10.81 (VAA), U10.82 (VAA), U10.119 (VAA), U10.120 (VAA), U10.121 (VAA), U10.122 (VAA), U10.123 (VAA), U10.132 (VAA), U10.141 (VAA), U10.142 (VAA), U10.149 (VAA), U10.158 (VAA), U10.159 (VAA), U10.160 (VAA)
/pal-ntsc.sch/Y-VIDEO: D1.2 (K), D2.1 (A), R3.1, U10.156 (VID0_Y)
/pal-ntsc.sch/Y_SYNC: R20.2, R35.2, U10.6 (OUT_Y)
//PCRD: RR3.7, U11.72 (RD#), U23.46, U24.133
//PCWR: RR3.5, U11.74 (WR#), U23.47, U24.132
GND: BUS1.A18 (GND), BUS1.A24 (GND), BUS1.A30 (GND), BUS1.A35 (GND), BUS1.A37 (GND), BUS1.A42 (GND), BUS1.A48 (GND), BUS1.A56 (GND), BUS1.B3 (GND), BUS1.B15 (GND), BUS1.B17 (GND), BUS1.B22 (GND), BUS1.B28 (GND), BUS1.B34 (GND), BUS1.B38 (GND), BUS1.B46 (GND), BUS1.B49 (M66EN), BUS1.B57 (GND), C2.2, C6.2, C7.2, C9.2, C10.2, C11.2, C12.2, C13.2, C14.2, C15.2, C16.2, C17.2, C18.2, C19.2, C20.2, C21.2, C22.2, C23.2, C24.2, C25.2, C26.2, C27.2, C28.2, C29.2, C30.2, C31.2, C32.1, C33.2, C37.1, C38.2, C43.2, C44.2, C45.2, C46.2, C47.2, C48.1, C49.2, C50.2, C51.2, C52.2, C53.2, C54.2, C55.2, C56.2, C57.2, C62.2, C63.2, C64.2, C65.1, C66.1, C67.2, C68.2, C69.2, C70.2, C71.2, C72.2, C73.2, CV1.2, D1.1 (A), D3.1 (A), J4.4, J4.5, J4.6, J4.7, L6.3 (COMMUN), P1.2 (Ext), P2.2 (Ext), P3.2 (Ext), P4.2 (PM), P5.1, P8.2 (Ext), P12.1, POT1.1, POT1.2, R8.2, R14.2, R15.1, R31.1, R32.2, R33.2, R34.2, R37.1, R38.2, R42.1, R43.1, R44.1, R45.2, R46.2, R47.2, U1.1 (A0), U1.2 (A1), U1.3 (A2), U1.4 (GND), U2.20 (GND), U3.10 (GND), U4.10 (GND), U5.10 (GND), U6.10 (GND), U7.3 (GND), U8.2 (GND), U8.3 (GND), U8.21 (RREF-), U8.22 (GREF-), U8.23 (BREF-), U8.41 (GND), U8.42 (GND), U8.61 (BLEVEL), U8.63 (GLEVEL), U8.67 (RLEVEL), U9.3 (GND), U9.4 (GND), U9.12 (OL2), U9.13 (OL3), U9.31 (GND), U9.32 (GND), U10.3 (YREF-), U10.5 (GNDA), U10.7 (YLEVEL), U10.16 (GND), U10.30 (GND), U10.44 (GND), U10.56 (GND), U10.66 (GND), U10.75 (GND), U10.88 (TDI), U10.89 (TMS), U10.90 (TCLK), U10.98 (GND), U10.103 (GND), U10.111 (GND), U10.116 (GNDA), U10.118 (CREF-), U10.124 (GNDA), U10.126 (GNDA), U10.128 (GNDA), U10.130 (GNDA), U10.134 (GNDA), U10.136 (GNDA), U10.138 (GNDA), U10.139 (GNDA), U10.143 (GNDA), U10.145 (GNDA), U10.147 (GNDA), U10.151 (GNDA), U10.153 (GNDA), U10.155 (GNDA), U10.157 (GNDA), U11.10 (VSS), U11.30 (VSS), U11.50 (VSS), U11.70 (VSS), U11.90 (VSS), U11.110 (VSS), U11.130 (VSS), U11.150 (VSS), U12.1 (GND), U12.39 (GND), U12.72 (GND), U13.1 (GND), U13.39 (GND), U13.72 (GND), U14.1 (GND), U14.39 (GND), U14.72 (GND), U15.1 (GND), U15.39 (GND), U15.72 (GND), U16.1 (GND), U16.39 (GND), U16.72 (GND), U17.1 (GND), U17.39 (GND), U17.72 (GND), U18.1 (GND), U18.39 (GND), U18.72 (GND), U19.1 (GND), U19.39 (GND), U19.72 (GND), U20.10 (VSS), U20.17 (NTSC/PAL), U21.5 (GND), U22.1 (GND), U22.11 (GND), U22.23 (GND), U22.38 (GND), U22.49 (GND), U22.64 (GND), U22.77 (GND), U22.88 (GND), U23.4 (GND), U23.14 (GND), U23.26 (GND), U23.41 (GND), U23.52 (GND), U23.67 (GND), U23.80 (GND), U23.91 (GND), U24.1 (GND), U24.10 (GND), U24.19 (GND), U24.29 (GND), U24.39 (GND), U24.51 (GND), U24.61 (GND), U24.70 (GND), U24.79 (GND), U24.91 (GND), U24.101 (GND), U24.110 (GND), U24.122 (GND), U24.131 (GND), U24.141 (GND), U24.151 (GND), W1.1, W2.1, W3.1, W4.1, W5.1
unnamed: BUS1.B9 (PRSNT1#), W5.2
unnamed: BUS1.B11 (PRSNT2#), W4.2
unnamed: BUS1.A4 (TDI), BUS1.B4 (TDO)
unnamed: C1.1, C47.1, R35.1
unnamed: C3.1, R3.2
unnamed: C4.1, R2.2
unnamed: C5.2, R19.1
unnamed: C8.2, R20.1
unnamed: C36.2, C37.2, R36.1
unnamed: C39.2, R24.2
unnamed: C40.2, R23.2
unnamed: C41.2, R22.2
unnamed: C46.1, C53.1, L1.2
unnamed: C49.1, R21.1, R26.2, X1.1
unnamed: C61.1, R30.1, R31.2
unnamed: CV1.1, X3.1
unnamed: D6.1 (A), R13.2
unnamed: L6.1, R10.1
unnamed: P4.1, R48.2, U23.25 (M1), U23.27 (M0), U23.29 (M2)
unnamed: POT1.3, R9.1
unnamed: Q1.2 (B), R16.1
unnamed: Q1.1 (E), R32.1, R39.2
unnamed: Q2.2 (B), R17.1
unnamed: Q2.1 (E), R33.1, R40.1
unnamed: Q3.2 (B), R18.1
unnamed: Q3.1 (E), R34.1, R41.2
unnamed: R28.2, U1.6 (SCL), U11.128 (ERD#/SCL)
unnamed: R29.2, U1.5 (SDA), U11.127 (EWR#/SDA)
unnamed: U8.58 (BIN), U8.68 (BOUT)
unnamed: C41.1, U8.75 (BVID0)
unnamed: R36.2, U8.6 (CEXT1)
unnamed: C36.1, R15.2, U8.7 (CEXT2)
unnamed: U8.60 (GIN), U8.70 (GOUT)
unnamed: C40.1, U8.79 (GVID0)
unnamed: U8.62 (RIN), U8.72 (ROUT)
unnamed: R38.1, U8.69 (RSET)
unnamed: C39.1, U8.83 (RVID0)
unnamed: C35.2, U9.41 (COMP), U9.42 (OPA)
unnamed: C34.2, C42.2, R8.1, U9.40 (IREF)
unnamed: C32.2, U9.43 (VREF), U9.44 (VREFOUT)
unnamed: C7.1, R27.2, U10.114 (CLEVEL)
unnamed: C6.1, R12.1, U10.113 (REFOUT), U10.137 (CREF+), U10.144 (YREF+)
unnamed: C16.1, U10.110 (N/C)
unnamed: R19.2, U10.115 (OUT_C)
unnamed: R27.1, U10.135 (R/2)
unnamed: C1.2, R14.1, U10.140 (SYNC_DET)
unnamed: C5.1, U10.117 (VIN_C)
unnamed: C8.1, U10.4 (VIN_Y/COMP.)
unnamed: C66.2, R25.1, U10.108 (XTAL1_IN), X2.2
unnamed: C65.2, R25.2, U10.109 (XTAL1_OUT), X2.1
unnamed: R6.1, U11.138 (FLT#), W2.2
unnamed: R5.1, U11.59 (MODE_16/32), W1.2
unnamed: R7.1, U11.135 (SNV), W3.2
unnamed: C58.1, U20.11 (B)
unnamed: R9.2, U20.21 (B/ADJ)
unnamed: C61.2, U20.24 (CS)
unnamed: C45.1, U20.15 (FLT)
unnamed: C59.1, U20.9 (G)
unnamed: R4.1, U20.2 (MCTR)
unnamed: L1.1, U20.18 (NOTCH)
unnamed: U20.23 (OSC), X3.2
unnamed: C60.1, U20.7 (R)
unnamed: C44.1, U20.6 (UOFF)
unnamed: C54.1, L2.2, U20.8 (VCC)
unnamed: C43.1, U20.12 (VOFF)
unnamed: C48.2, C64.1, R11.2, U20.13 (VREF)
unnamed: L6.2, R11.1, U20.20 (Y+SIN)
unnamed: R10.2, U20.22 (Y+SOUT)
unnamed: P10.1, U23.87
unnamed: P11.1, U23.82 (PGCK4)
unnamed: P9.1, U23.51 (SGCK3)
